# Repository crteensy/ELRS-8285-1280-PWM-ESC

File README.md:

# ELRS-8285-1280-PWM-ESC
A 2.4 GHz ELRS resceiver with 4 PWM outputs and a 1S, 5A ESC

### Revision 1.1
- should now be more robust with two servos on one channel through a Y cable
 - adjusted pull-up value on PWM1
 - added pull-up on PWM2
- this required a minor layout change for the added pull-up

### Overview:
- 2.4 GHz ExpressLRS receiver, ESP8285 based, with WiFi antenna
- 4 Servo PWM outputs
- on-board ESC
 - Up to 5.5 V input voltage (1S LiPo or HV-LiPo)
 - BLHeli_S I_H_40 (I didn't test if deadtime can be reduced - it probably can)
 - Handled 5 A for over a minute on the bench without damage: bench power supply set to 4.5 V, Mamba 1408 4000KV, HQProp DP 4x3x3. There was a cover over the ESC to reduce airflow from the prop.
- Voltage divider to measure battery voltage (not yet supported by ExpressLRS, 20211230)
- Testpads to flash ESC firmware through the EFM8's UART - can also be used with an external flight controller and serial passthrough to configure the ESC and re-flash it
- ExpressLRS can be flashed through the servo header

RCGroups discussion thread: https://www.rcgroups.com/forums/showthread.php?4040599-DIY-ExpressLRS-2G4-Rx-with-4xPWM-output-and-an-on-board-1S-ESC#post48415931

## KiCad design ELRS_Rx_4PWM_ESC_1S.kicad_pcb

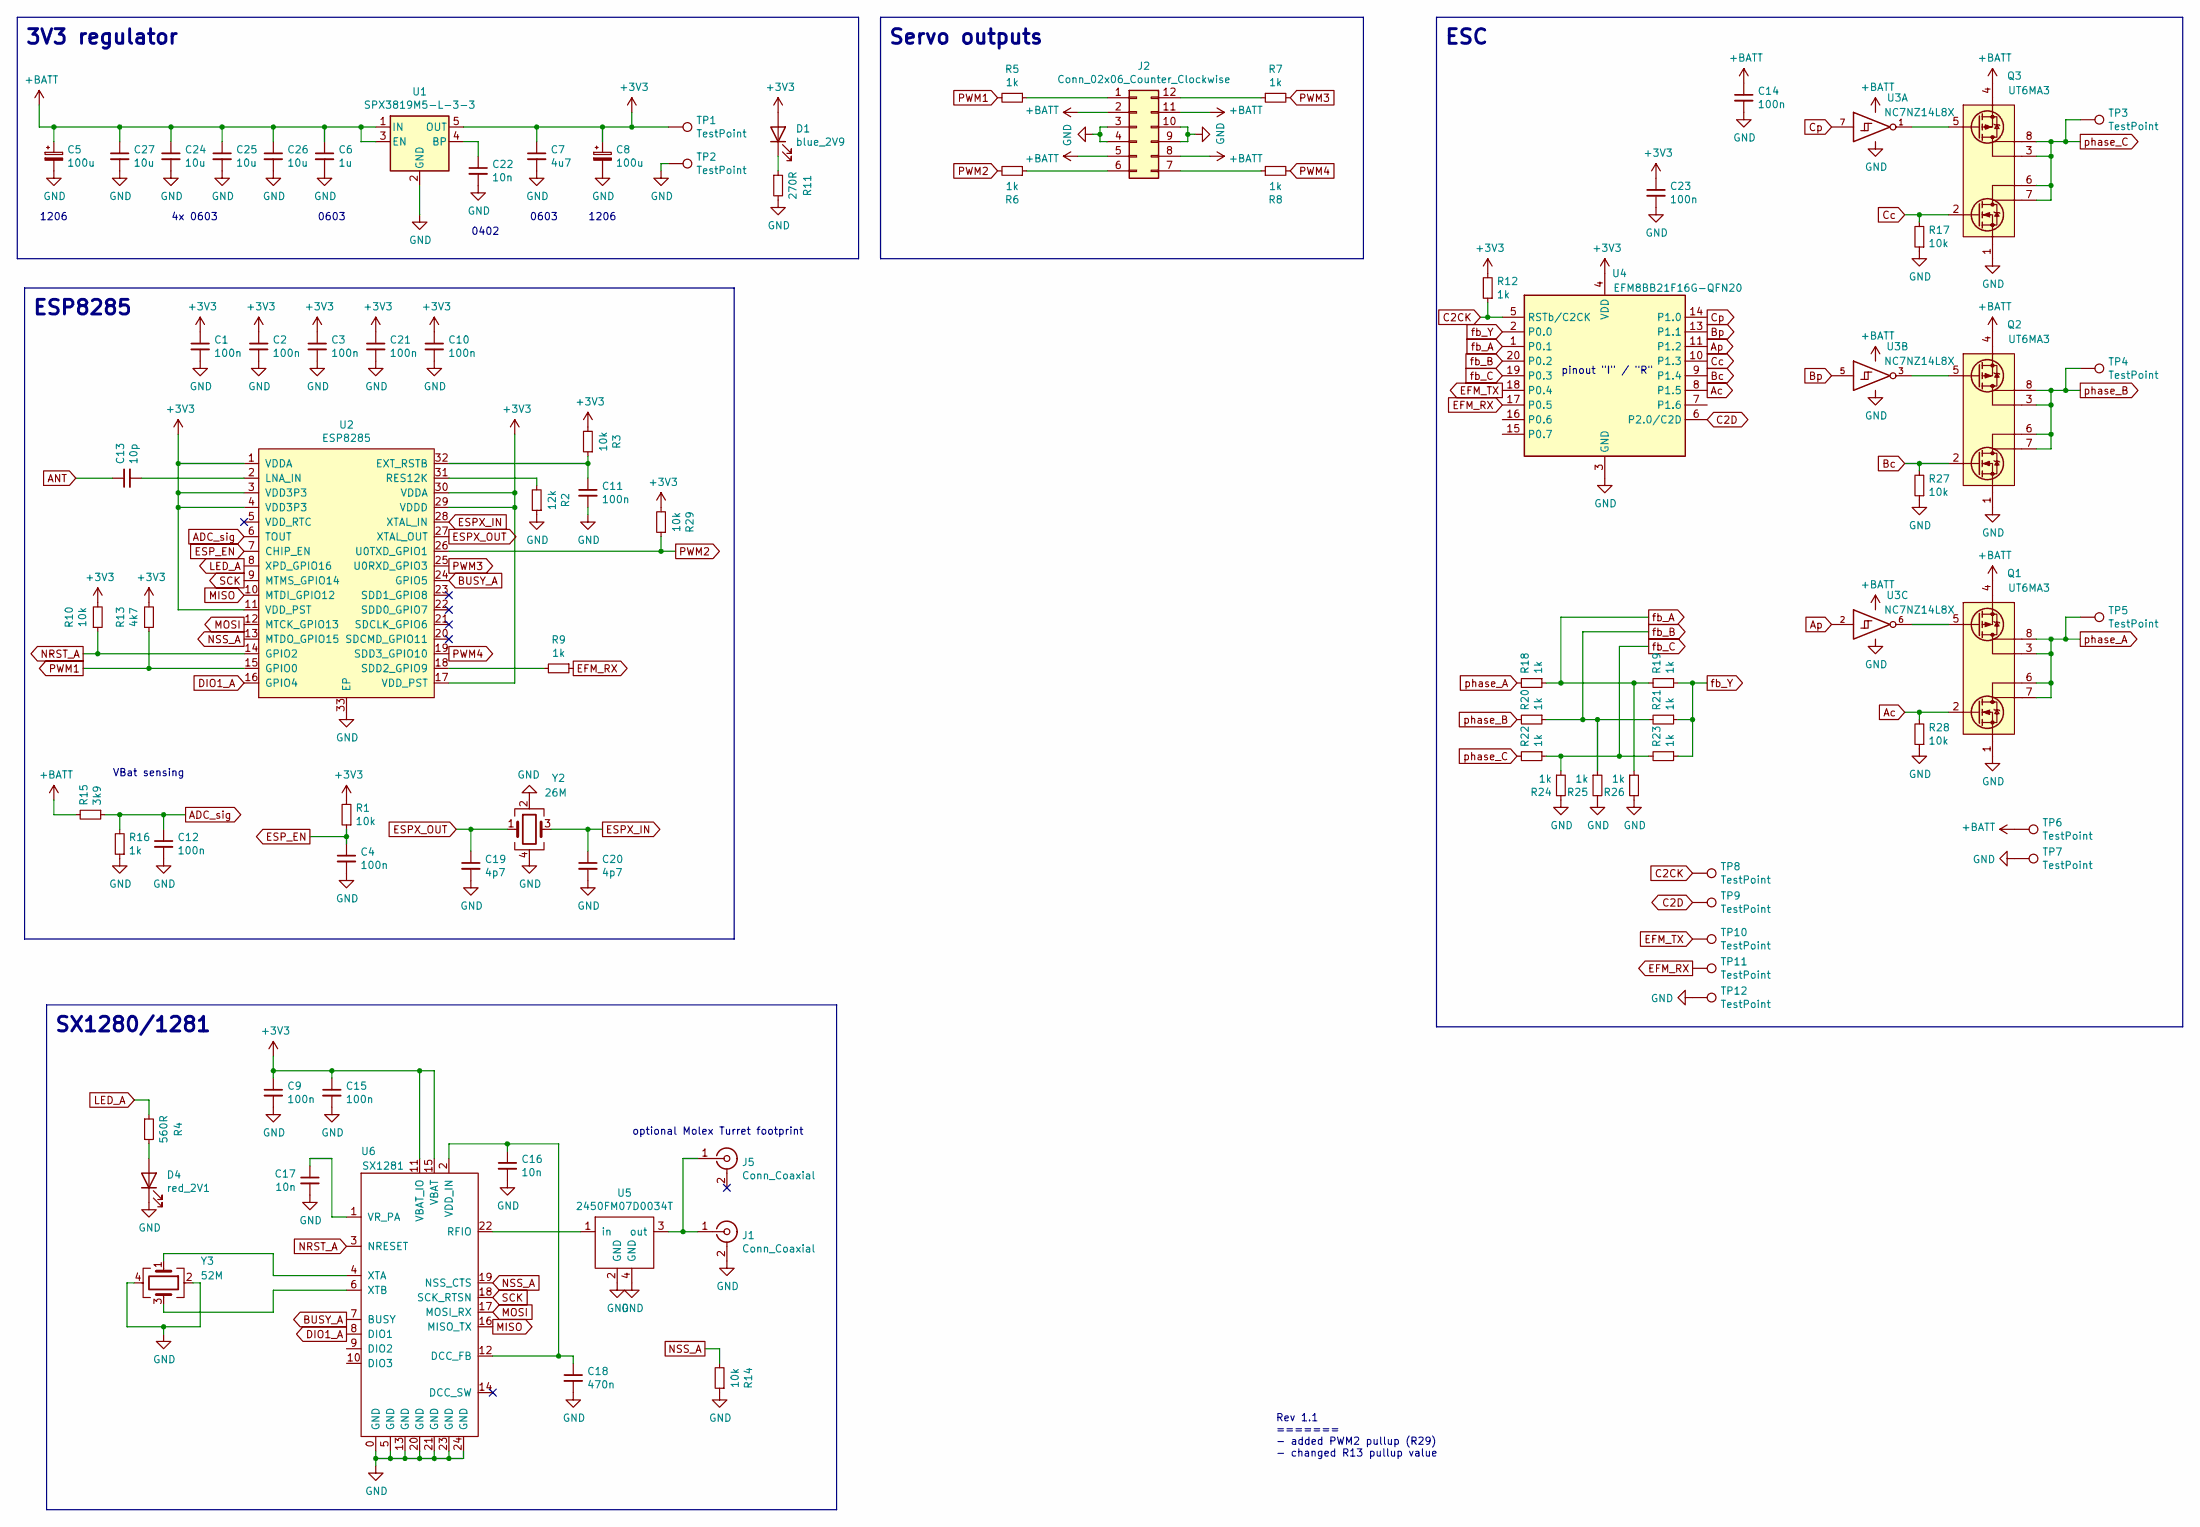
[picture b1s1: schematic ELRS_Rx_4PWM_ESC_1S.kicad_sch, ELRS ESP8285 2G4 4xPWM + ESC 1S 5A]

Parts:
C1, C2, C3, C4, C9, C10, C11, C12, C14, C15, C21, C23: 100n; C_0402_1005Metric
C5, C8: 100u; CP_EIA-3216-18_Kemet-A
C6: 1u; C_0603_1608Metric
C7: 4u7; C_0603_1608Metric
C13: 10p; C_0402_1005Metric
C16, C17, C22: 10n; C_0402_1005Metric
C18: 470n; C_0402_1005Metric
C19, C20: 4p7; C_0402_1005Metric
C24, C25, C26, C27: 10u; C_0603_1608Metric
D1: blue_2V9; LED_0402_1005Metric
D4: red_2V1; LED_0402_1005Metric
J1: Conn_Coaxial; U.FL_Molex_MCRF_73412-0110_Vertical_dense
J2: Conn_02x06_Counter_Clockwise; BoardEdge_Servo_4
J5: Conn_Coaxial; molex_479480001_2g4-turret
Q1, Q2, Q3: UT6MA3; DFN-6-2EP_2x2mm_P0.65mm_EP2x0.9x0.7
R1, R3, R10, R14, R17, R27, R28, R29: 10k; R_0402_1005Metric
R2: 12k; R_0402_1005Metric
R4: 560R; R_0402_1005Metric
R5, R6, R7, R8, R9, R12, R16, R18, R19, R20, R21, R22, R23, R24, R25, R26: 1k; R_0402_1005Metric
R11: 270R; R_0402_1005Metric
R13: 4k7; R_0402_1005Metric
R15: 3k9; R_0402_1005Metric
TP1, TP2, TP8, TP9, TP10, TP11, TP12: TestPoint; TestPoint_Pad_D1.0mm
TP3, TP4, TP5, TP6, TP7: TestPoint; TestPoint_Pad_2.5x2.5mm
U1: SPX3819M5-L-3-3; SOT-23-5
U2: ESP8285; QFN-32-1EP_5x5mm_P0.5mm_EP3.7x3.7mm_dense
U3: NC7NZ14L8X; UQFN-8_1.6x1.6mm_P0.50mm
U4: EFM8BB21F16G-QFN20; SiliconLabs_QFN-20-1EP_3x3mm_P0.5mm_EP1.8x1.8mm
U5: 2450FM07D0034T
U6: SX1281; QFN-24-1EP_4x4mm_P0.5mm_EP2.6x2.6mm_SX1280_dense
Y2: 26M; Crystal_SMD_2016-4Pin_2.0x1.6mm
Y3: 52M; Crystal_SMD_2016-4Pin_2.0x1.6mm

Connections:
+3V3: C1.1, C2.1, C3.1, C7.1, C8.1, C9.1, C10.1, C15.1, C21.1, C23.1, D1.2 (A), R1.2, R3.2, R10.2, R12.2, R13.2, R29.2, TP1.1, U1.5 (OUT), U2.1 (VDDA), U2.3 (VDD3P3), U2.4 (VDD3P3), U2.11 (VDD_PST), U2.17 (VDD_PST), U2.29 (VDDD), U2.30 (VDDA), U4.4 (VDD), U6.11 (VBAT_IO), U6.15 (VBAT)
+BATT: C5.1, C6.1, C14.1, C24.1, C25.1, C26.1, C27.1, J2.2, J2.5, J2.8, J2.11, Q1.4 (S2), Q2.4 (S2), Q3.4 (S2), R15.2, TP6.1, U1.1 (IN), U1.3 (EN), U3.8 (VCC)
ADC_sig: C12.1, R15.1, R16.2, U2.6 (TOUT)
ANT: C13.1
Ac: Q1.2 (G1), R28.2, U4.8 (P1.5)
Ap: U3.2, U4.11 (P1.2)
BUSY_A: U2.24 (GPIO5), U6.7 (BUSY)
Bc: Q2.2 (G1), R27.2, U4.9 (P1.4)
Bp: U3.5, U4.13 (P1.1)
C2CK: R12.1, TP8.1, U4.5 (RSTb/C2CK)
C2D: TP9.1, U4.6 (P2.0/C2D)
Cc: Q3.2 (G1), R17.2, U4.10 (P1.3)
Cp: U3.7, U4.14 (P1.0)
DIO1_A: U2.16 (GPIO4), U6.8 (DIO1)
EFM_RX: R9.1, TP11.1, U4.17 (P0.5)
EFM_TX: TP10.1, U4.18 (P0.4)
ESPX_IN: C20.1, U2.28 (XTAL_IN), Y2.3
ESPX_OUT: C19.1, U2.27 (XTAL_OUT), Y2.1
ESP_EN: C4.1, R1.1, U2.7 (CHIP_EN)
GND: C1.2, C2.2, C3.2, C4.2, C5.2, C6.2, C7.2, C8.2, C9.2, C10.2, C11.2, C12.2, C14.2, C15.2, C16.2, C17.2, C18.2, C19.2, C20.2, C21.2, C22.2, C23.2, C24.2, C25.2, C26.2, C27.2, D4.1 (K), J1.2 (Ext), J2.3, J2.4, J2.9, J2.10, Q1.1 (S1), Q2.1 (S1), Q3.1 (S1), R2.1, R11.2, R14.1, R16.1, R17.1, R24.2, R25.2, R26.2, R27.1, R28.1, TP2.1, TP7.1, TP12.1, U1.2 (GND), U2.33 (EP), U3.4 (GND), U4.3 (GND), U4.12 (GND), U4.21 (GND), U5.2 (GND), U5.4 (GND), U6.0 (GND), U6.5 (GND), U6.13 (GND), U6.20 (GND), U6.21 (GND), U6.23 (GND), U6.24 (GND), Y2.2, Y2.4, Y3.2, Y3.4
LED_A: R4.1, U2.8 (XPD_GPIO16)
MISO: U2.10 (MTDI_GPIO12), U6.16 (MISO_TX)
MOSI: U2.12 (MTCK_GPIO13), U6.17 (MOSI_RX)
NRST_A: R10.1, U2.14 (GPIO2), U6.3 (NRESET)
NSS_A: R14.2, U2.13 (MTDO_GPIO15), U6.19 (NSS_CTS)
unnamed: C11.1, R3.1, U2.32 (EXT_RSTB)
unnamed: C13.2, U2.2 (LNA_IN)
unnamed: C16.1, C18.1, U6.2 (VDD_IN), U6.12 (DCC_FB)
unnamed: C17.1, U6.1 (VR_PA)
unnamed: C22.1, U1.4 (BP)
unnamed: D1.1 (K), R11.1
unnamed: D4.2 (A), R4.2
unnamed: J1.1 (In), J5.1 (In), U5.3 (out)
unnamed: J2.1, R5.1
unnamed: J2.6, R6.1
unnamed: J2.7, R8.1
unnamed: J2.12, R7.1
unnamed: Q1.5 (G2), U3.6
unnamed: Q2.5 (G2), U3.3
unnamed: Q3.5 (G2), U3.1
unnamed: R2.2, U2.31 (RES12K)
unnamed: R9.2, U2.18 (SDD2_GPIO9)
unnamed: U5.1 (in), U6.22 (RFIO)
unnamed: U6.4 (XTA), Y3.1
unnamed: U6.6 (XTB), Y3.3
PWM1: R5.2, R13.1, U2.15 (GPIO0)
PWM2: R6.2, R29.1, U2.26 (U0TXD_GPIO1)
PWM3: R7.2, U2.25 (U0RXD_GPIO3)
PWM4: R8.2, U2.19 (SDD3_GPIO10)
SCK: U2.9 (MTMS_GPIO14), U6.18 (SCK_RTSN)
fb_A: R18.1, R19.2, R26.1, U4.1 (P0.1)
fb_B: R20.1, R21.2, R25.1, U4.20 (P0.2)
fb_C: R22.1, R23.2, R24.1, U4.19 (P0.3)
fb_Y: R19.1, R21.1, R23.1, U4.2 (P0.0)
phase_A: Q1.3 (D2), Q1.6 (D1), Q1.7 (D1), Q1.8 (D2), R18.2, TP5.1
phase_B: Q2.3 (D2), Q2.6 (D1), Q2.7 (D1), Q2.8 (D2), R20.2, TP4.1
phase_C: Q3.3 (D2), Q3.6 (D1), Q3.7 (D1), Q3.8 (D2), R22.2, TP3.1

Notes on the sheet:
Rev 1.1 ======= - added PWM2 pullup (R29) - changed R13 pullup value
optional Molex Turret footprint
1206
3V3 regulator
ESP8285
0603
pinout "I" / "R"
SX1280/1281
0402
VBat sensing
ESC
4x 0603
Servo outputs

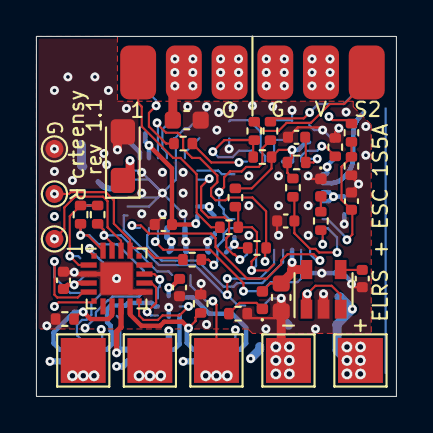
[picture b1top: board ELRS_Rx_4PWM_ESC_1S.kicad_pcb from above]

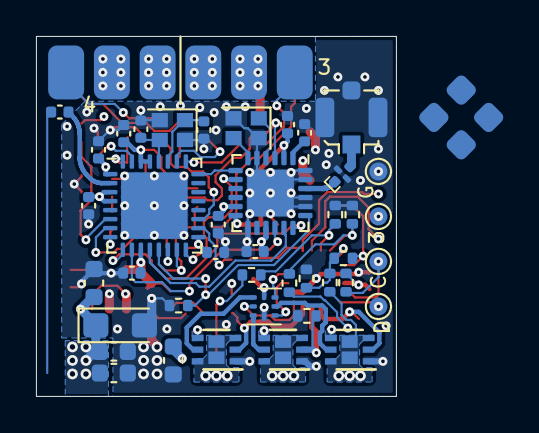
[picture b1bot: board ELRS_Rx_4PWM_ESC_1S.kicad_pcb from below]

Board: 4 copper layers, 20.0 x 20.0 mm, 84 parts (42 on the bottom side), 56 nets.

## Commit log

2021-12-30 initial commit (kicad, readme)
2021-12-30 minor layout fix
2022-09-15 V1.1 adjust pull-up resistors and layout
2022-09-15 fix top silkscreen
